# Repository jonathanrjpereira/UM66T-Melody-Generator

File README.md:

# UM66T Melody Generator
An UM66T generates various Melody Tunes when triggered which can be used in car/scooter reverse signals, doorbells and toys.

**Full Video:**

**Order PCB:**  [PCBWay](https://www.pcbway.com/project/shareproject/Musical_Bell.html)

## Electronic Components
| Qty | Component | Buy |
| ------------- | ------------- | ------------- |
| 1 | IC UM66T |[AliExpress](http://s.click.aliexpress.com/e/tNfC3kG) |
| 1 | 100Ω 220Ω 4.7KΩ Resistor |[AliExpress](http://s.click.aliexpress.com/e/bh4eqrQs) |
| 1 | BC547 Transistor |[AliExpress](http://s.click.aliexpress.com/e/cYm6Rss0) |
| 1 | SPDT Slide Switch |[AliExpress](http://s.click.aliexpress.com/e/cAs918wG) |
| 1 | 5mm LED |[AliExpress](http://s.click.aliexpress.com/e/wuFpLXS) |
| 1 | 100uF Capacitor |[AliExpress](http://s.click.aliexpress.com/e/c9FHzl5W) |
| 1 | 0.1uF Capacitor |[AliExpress](http://s.click.aliexpress.com/e/SX7eHuG) |
| 1 | Speaker |[AliExpress](http://s.click.aliexpress.com/e/brMJh46c) |
| 1 | 5VDC Adapter |[AliExpress](http://s.click.aliexpress.com/e/V0x0bms) |
| 1 | PCB |[AliExpress](http://s.click.aliexpress.com/e/dhgwzKY) |

| Tools | Buy |
|--|--|
|Soldering Iron|[AliExpress](http://s.click.aliexpress.com/e/E83bSJI) |
|Soldering Wire|[AliExpress](http://s.click.aliexpress.com/e/PdhB0nm) |
|Mini PCB Hand Drill + Bits|[AliExpress](http://s.click.aliexpress.com/e/b93tomjI) |
|Wire Cutter|[AliExpress](http://s.click.aliexpress.com/e/bHFL9vLi) |
|Wire Stripper|[AliExpress](http://s.click.aliexpress.com/e/4yJWedw) |
|Soldering Helping Hands|[AliExpress](http://s.click.aliexpress.com/e/cAQ2StNm) |

## Working
**UM66T:**

The UM66T is an CMOS LSI designed for musical applications and has an on-chip ROM
containing a musical tune. The deice has very low power consumption (around 180mW)
since it is fabricated using the CMOS process. The IC includes an inbuilt oscillation
circuit. Hence a compact melody module can be constructed with only a few additional
components.

An input trigger enables the tone generator unit which in turn drives an external speaker unit.
The tone generator unit consists of the Oscillator, Rhythm generator, Tempo generator and ROM.
The oscillator frequency is used as a time for tone and beat generators. Its accuracy affects the quality of the
music.

A 5VDC power adapter is used as the power supply. Since the UM66T has a maximum supply voltage of 4.5V,
a 100Ω resistor is used to reduce the supply voltage to a suitable 3.3V.
When the SPDT slide switch is turned ON, the UM66T is triggered and produces a melody signal that begins
from the first note due to the power on reset feature. An external transistor amplifies the signal and it's output is
connected to a speaker. An LED turns on whenever the circuit is triggered.

## Contributing🛠
Are you an engineer or hobbyist who has a great idea for a new feature in this project? Maybe you have a good idea for a bug fix? Feel free to grab our code & schematics from GitHub and tinker with it. Don't forget to smash ⭐️ & the Pull Request button.

[![alt text][1.1]][1] [![alt text][2.1]][2] [![alt text][3.1]][3]

[1.1]: https://github.com/jonathanrjpereira/Social-Media-README/blob/master/youtube.png (YouTube)
[2.1]: https://github.com/jonathanrjpereira/Social-Media-README/blob/master/instagram.png (Instagram)
[3.1]: https://github.com/jonathanrjpereira/Social-Media-README/blob/master/github.png (GitHub)

[1]: https://www.youtube.com/channel/UCRW-41O1vy98KKgJRQoYzdg
[2]: https://www.instagram.com/electroguruji/
[3]: https://github.com/jonathanrjpereira

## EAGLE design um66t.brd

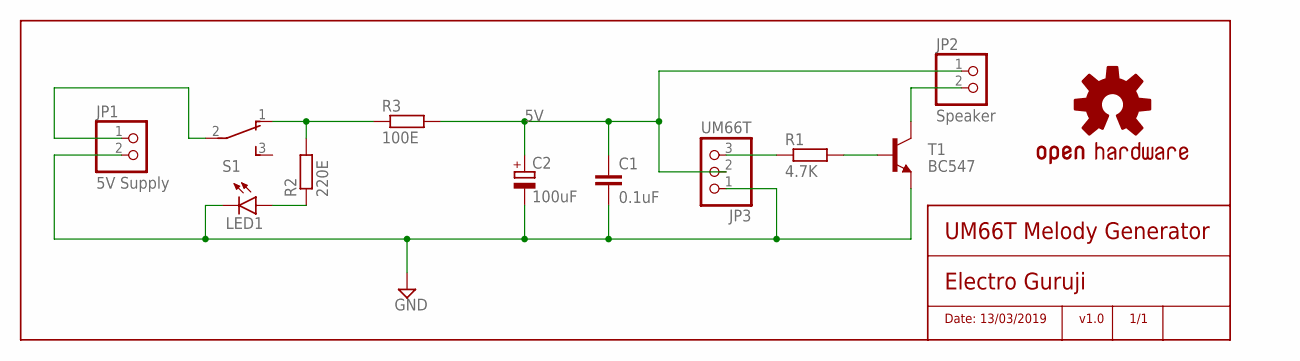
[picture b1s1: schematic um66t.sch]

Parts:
C1: 0.1uF; C025-024X044
C2: 100uF; E5-5
JP1: 5V Supply; 1X02
JP2: Speaker; 1X02
JP3: UM66T; 1X03
LED1: LED5MM
LOGO1: OSHW-LOGOM-COPPER; OSHW-LOGO-M_COPPER
R1: 4.7K; 0204/5
R2: 220E; 0204/5
R3: 100E; 0204/5
S1: SPDT; TL3XYO
T1: BC547; TO92-CBE

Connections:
5V: C1.1, C2.+, JP2.1, JP3.2, R3.2
9V: JP1.1, S1.2
GND: C1.2, C2.-, JP1.2, JP3.1, LED1.K (C), T1.E
unnamed: LED1.A, R2.1
unnamed: R2.2, R3.1, S1.1 (O)
unnamed: JP3.3, R1.1
unnamed: R1.2, T1.B
unnamed: JP2.2, T1.C

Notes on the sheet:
UM66T Melody Generator
Electro Guruji
Date: 13/03/2019
v1.0
1/1

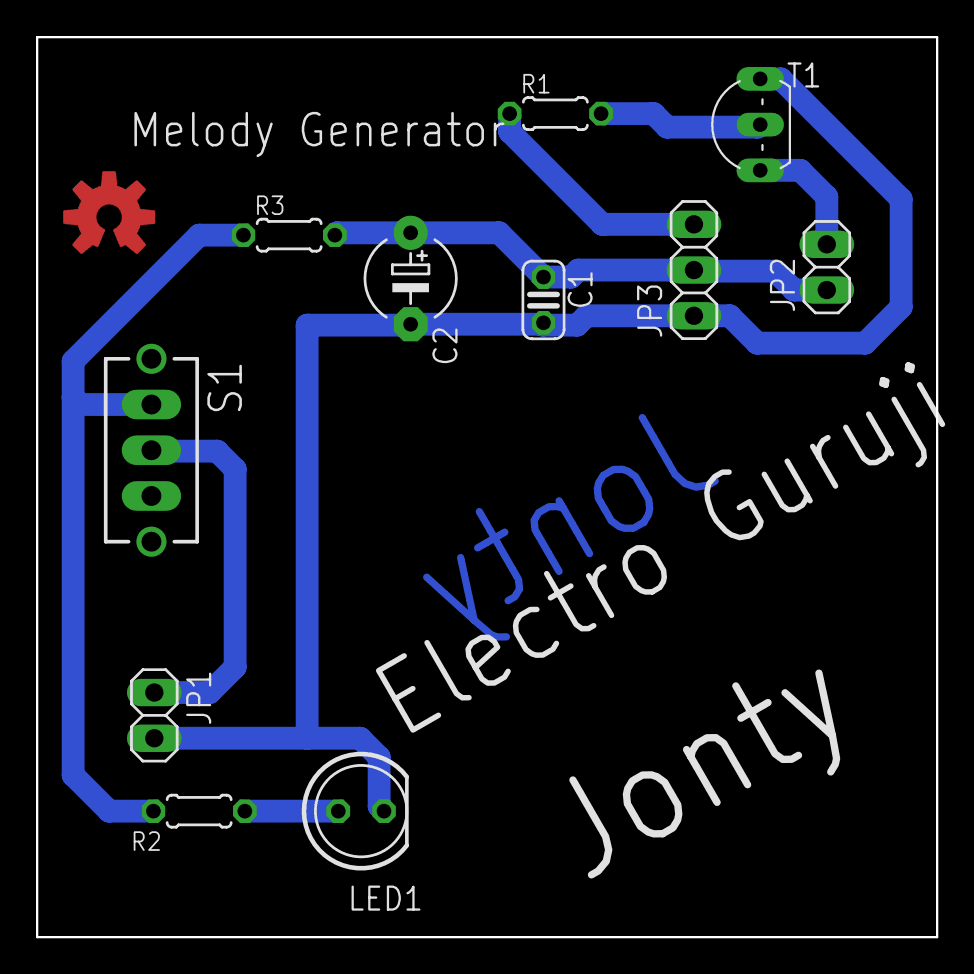
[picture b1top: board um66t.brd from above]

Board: 2 copper layers, 50.0 x 50.0 mm, 12 parts (0 on the bottom side), 8 nets.

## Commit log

2019-03-13 Schematic
2019-03-13 Board
2019-03-13 Working + BD + pinout/descrption
2019-03-13 Datasheet + Components
2019-03-27 Replaced 7833 with 10E resistor
    Changed BC547 Package
2019-03-27 Changed 9V Battery to 5V Supply
2019-04-03 9V battery replaced by 5VDC Power adapter
2019-04-30 Gerber Files
2019-05-01 Order PCB Link & Video

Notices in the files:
parts and their libraries:
SparkFun-Aesthetics: Licensing: Creative Commons ShareAlike 4.0 International - https://creativecommons.org/licenses/by-sa/4.0
